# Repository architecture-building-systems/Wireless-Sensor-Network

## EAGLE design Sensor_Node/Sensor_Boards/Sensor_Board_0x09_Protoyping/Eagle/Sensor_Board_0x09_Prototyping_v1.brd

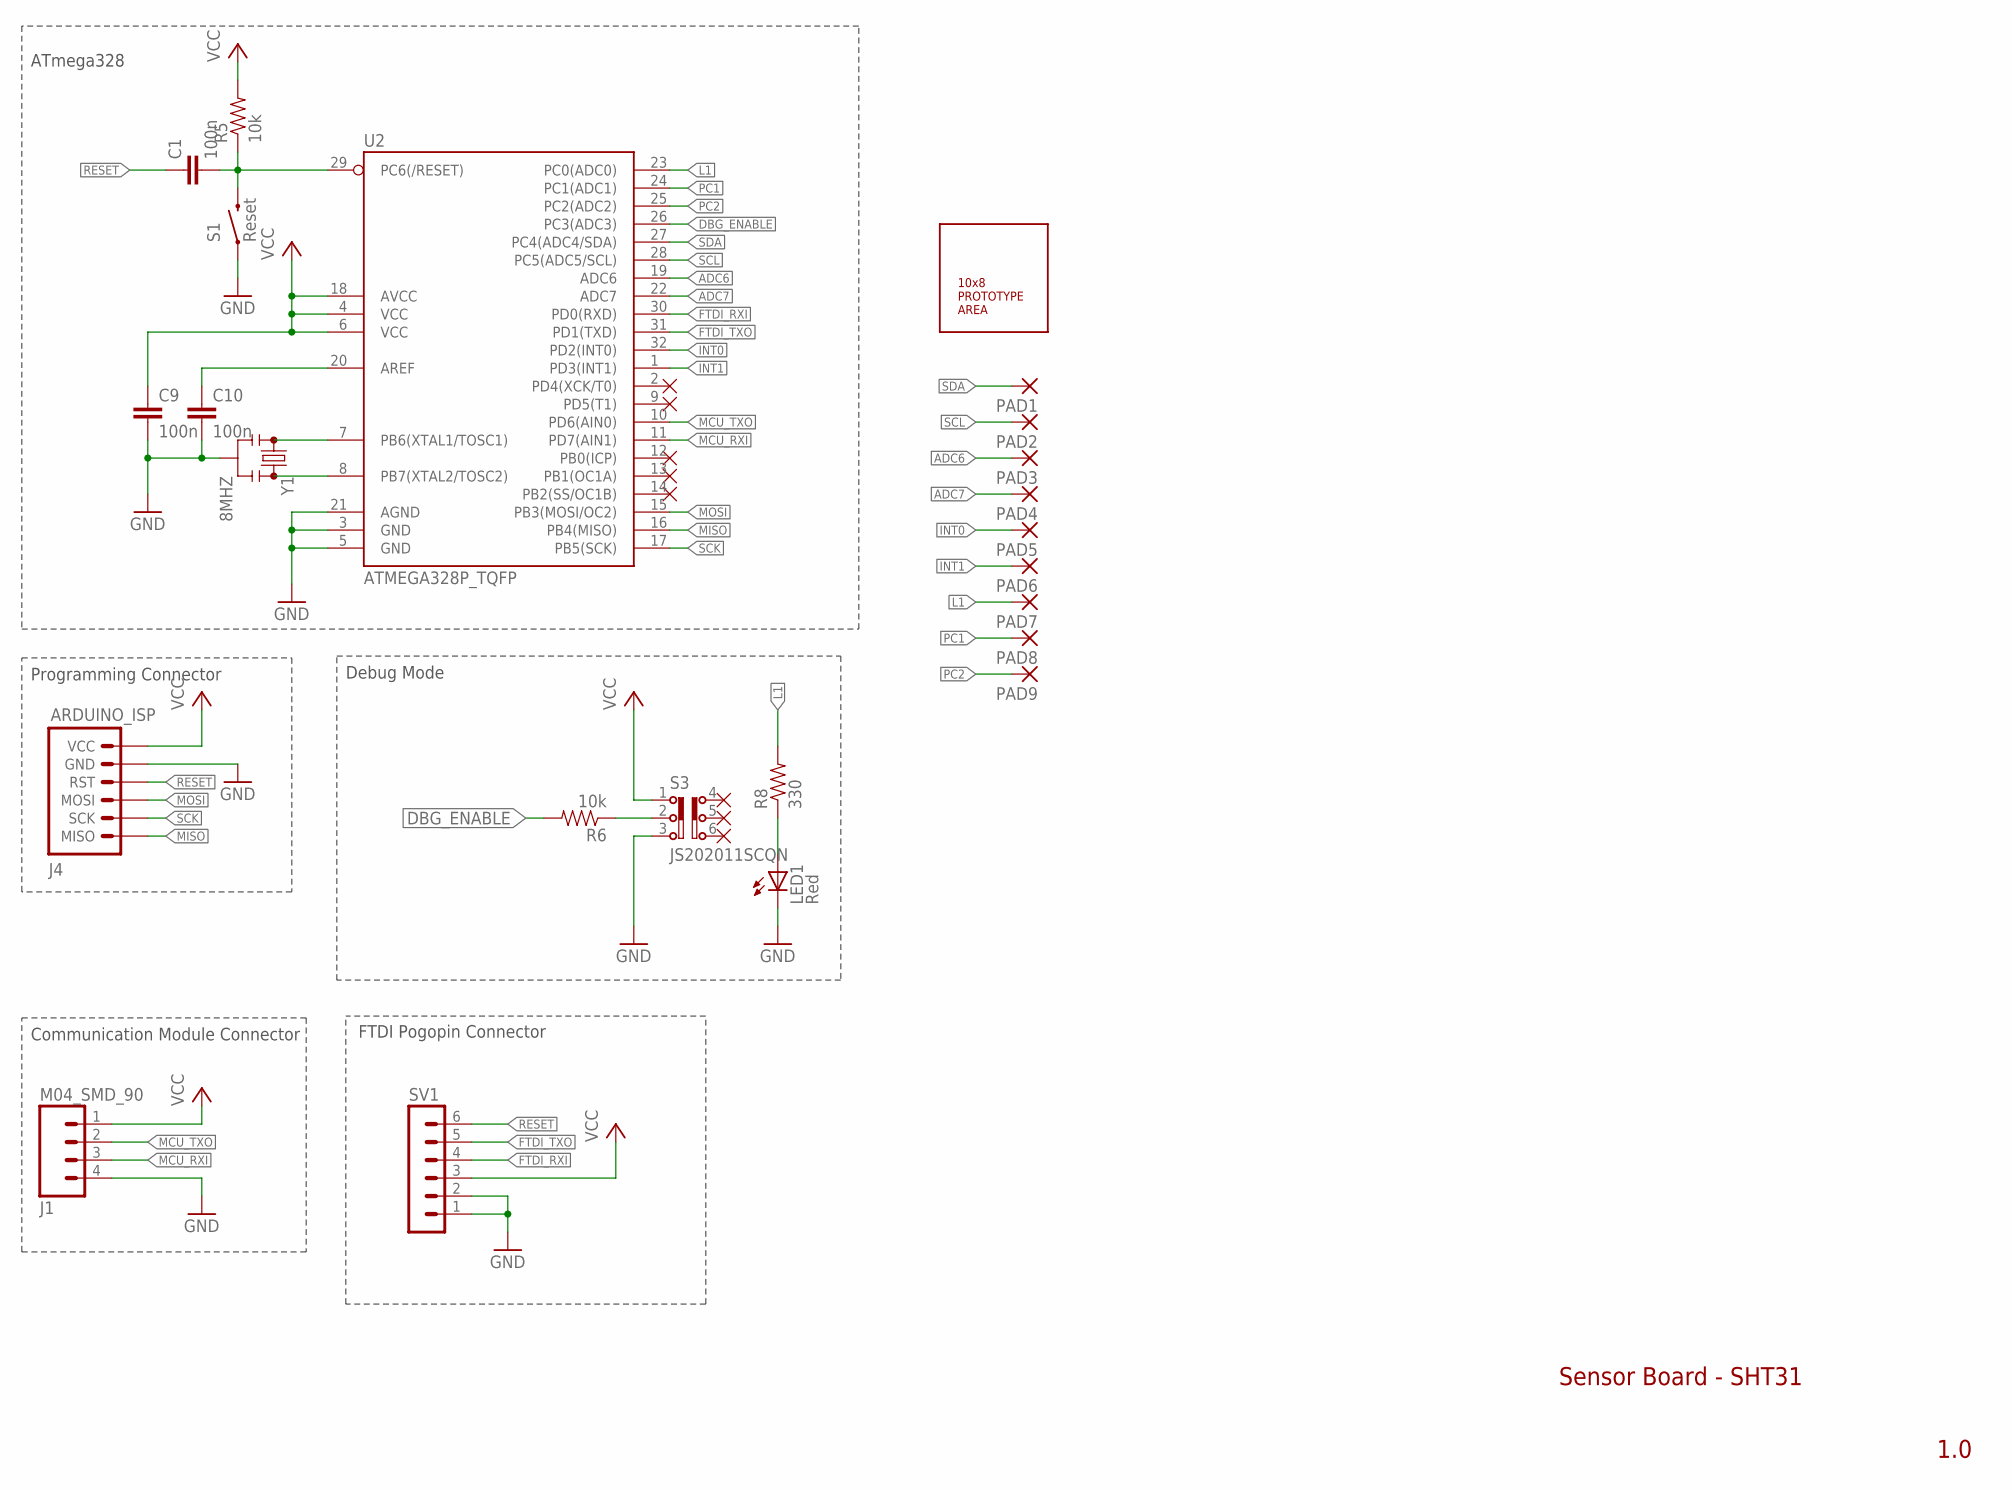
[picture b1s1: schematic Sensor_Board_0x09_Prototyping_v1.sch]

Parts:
C1, C9, C10: 100n; C0805
J1: M04_SMD_90
J4: ARDUINO_ISP; M-2X3
LED1: Red; SML0805
PAD1, PAD2, PAD3, PAD4, PAD5, PAD6, PAD7, PAD8, PAD9: 1,6/0,9
R5, R6: 10k; 0805
R8: 330; 0805
S1: Reset; M-PUSHBUTTON-SMD
S3: JS202011SCQN
SV1: MA06-1
U2: ATMEGA328P_TQFP; TQFP32-08
U$1: 10X8_PROTOTYPE_AREA
Y1: 8MHZ; RESONATOR-SMD

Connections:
ADC6: PAD3.1, U2.19 (ADC6)
ADC7: PAD4.1, U2.22 (ADC7)
DBG_ENABLE: R6.2, U2.26 (PC3(ADC3))
FTDI_RXI: SV1.4, U2.30 (PD0(RXD))
FTDI_TXO: SV1.5, U2.31 (PD1(TXD))
GND: C9.2, C10.2, J1.4, J4.P$5 (GND), LED1.C, S1.1 (LEFT), S1.2 (LEFT), S3.3, SV1.1, SV1.2, U2.3 (GND), U2.5 (GND), U2.21 (AGND), Y1.2
INT0: PAD5.1, U2.32 (PD2(INT0))
INT1: PAD6.1, U2.1 (PD3(INT1))
L1: PAD7.1, R8.2, U2.23 (PC0(ADC0))
MCU_RXI: J1.3, U2.11 (PD7(AIN1))
MCU_TXO: J1.2, U2.10 (PD6(AIN0))
MISO: J4.P$1 (MISO), U2.16 (PB4(MISO))
MOSI: J4.P$3 (MOSI), U2.15 (PB3(MOSI/OC2))
unnamed: U2.8 (PB7(XTAL2/TOSC2)), Y1.3
unnamed: U2.7 (PB6(XTAL1/TOSC1)), Y1.1
unnamed: R6.1, S3.2
unnamed: C1.2, R5.1, S1.3 (RIGHT), S1.4 (RIGHT), U2.29 (PC6(/RESET))
unnamed: C10.1, U2.20 (AREF)
unnamed: LED1.A, R8.1
PC1: PAD8.1, U2.24 (PC1(ADC1))
PC2: PAD9.1, U2.25 (PC2(ADC2))
RESET: C1.1, J4.P$4 (RST), SV1.6
SCK: J4.P$2 (SCK), U2.17 (PB5(SCK))
SCL: PAD2.1, U2.28 (PC5(ADC5/SCL))
SDA: PAD1.1, U2.27 (PC4(ADC4/SDA))
VCC: C9.1, J1.1, J4.P$6 (VCC), R5.2, S3.1, SV1.3, U2.4 (VCC), U2.6 (VCC), U2.18 (AVCC)

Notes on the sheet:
Debug Mode
Programming Connector
ATmega328
Communication Module Connector
Sensor Board - SHT31
1.0
FTDI Pogopin Connector

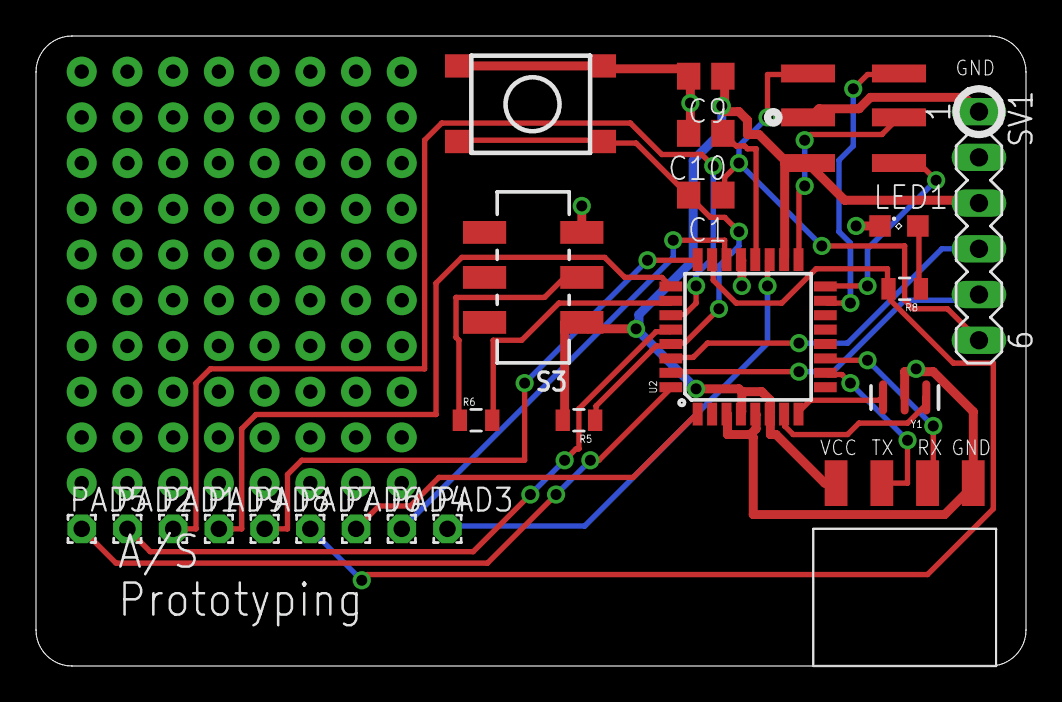
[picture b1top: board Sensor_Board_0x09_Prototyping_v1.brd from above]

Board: 2 copper layers, 55.0 x 35.0 mm, 24 parts (0 on the bottom side), 26 nets.

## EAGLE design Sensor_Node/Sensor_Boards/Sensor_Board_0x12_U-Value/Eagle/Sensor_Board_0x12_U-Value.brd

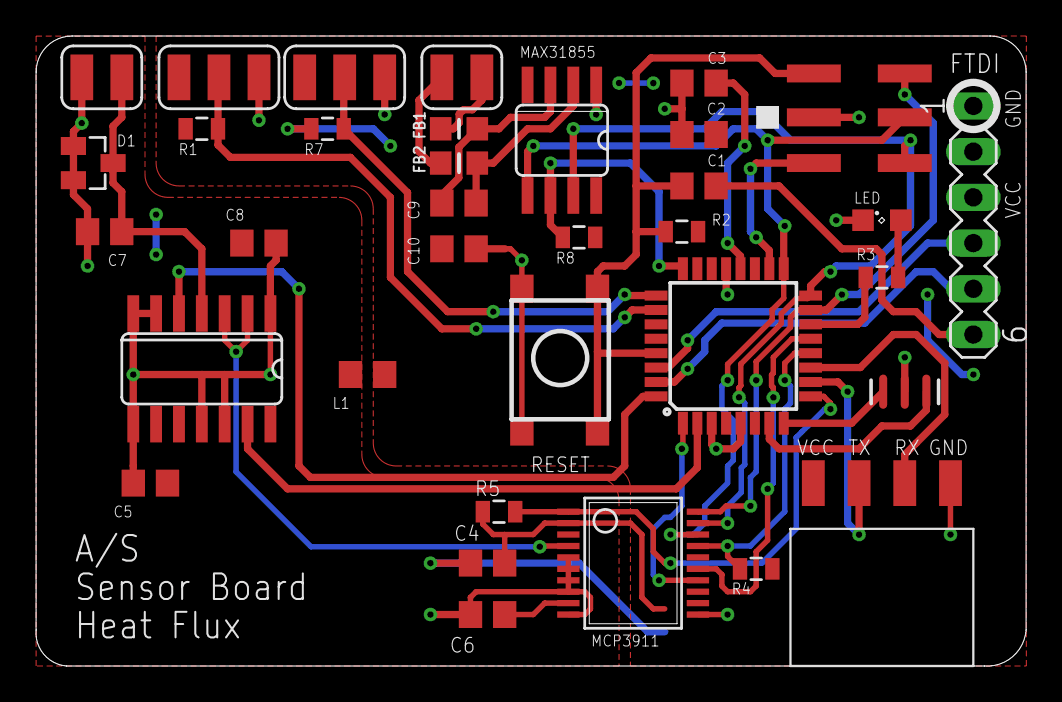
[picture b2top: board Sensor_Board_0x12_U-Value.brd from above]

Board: 2 copper layers, 55.0 x 35.0 mm, 42 parts (1 on the bottom side), 34 nets.

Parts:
C1, C2, C3, C4, C5, C6, C8, C10: 100n; C0805
C7: 1u; C0805
C9: 10n; C0805
D1: LEDXLAMP_BAV99; LEDXLAMP_SOT23
FB1, FB2: MICROBUILDER__0805MP
IC1: MCP3911; HEATFLOW_SSOP20
IC2: 40XX_4066D; 40XX_SO14
IC4: MAX31855; ADAFRUIT_SO08
J1: M04_SMD_90
J4: ARDUINO_ISP; M-2X3
L1: HEATFLOW2_74279220601; HEATFLOW2_0805
LED: Red; SML0805
PAD1, PAD2, PAD3, PAD4, PAD5, PAD6, PAD7, PAD8, PAD9, PAD10: WIREPADSMD1,27-254; SMD1,27-2,54
R1, R2, R4, R5, R7, R8: 10k; 0805
R3: 330; 0805
R6: 0; RESISTOR_M0805
S1: Reset; M-PUSHBUTTON-SMD
SV1: MA06-1
U2: ATMEGA328P_TQFP; TQFP32-08
Y1: 8MHZ; RESONATOR-SMD

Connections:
AGND: C4.1, C5.2, C7.2, C8.2, D1.1, D1.2, IC1.5, IC1.6, IC1.7, IC1.8, IC1.10, IC2.1, IC2.6, IC2.7, IC2.8, IC2.11, IC2.12, PAD2.1, R6.2
AVCC: C5.1, C8.1, IC1.3, IC2.14, L1.2
DGND: C2.2, C3.2, C6.2, C10.2, IC1.11, IC4.1, J1.4, J4.P$5, LED.C, PAD5.1, PAD8.1, R6.1, S1.1, S1.2, SV1.1, SV1.2, U2.3, U2.5, U2.21, Y1.2
DS18B20_DATA_1: PAD4.1, R1.1, U2.26
DS18B20_DATA_2: PAD7.1, R7.1, U2.25
DVCC: C2.1, C6.1, C10.1, IC1.2, IC4.4, J1.1, J4.P$6, L1.1, PAD3.1, PAD6.1, R1.2, R2.2, R4.2, R5.2, R7.2, R8.2, SV1.3, U2.4, U2.6, U2.18
FTDI_RESET: C1.1, SV1.6
FTDI_RXI: SV1.4, U2.30
FTDI_TXO: SV1.5, U2.31
INPUT_EN: IC2.5, U2.32
INPUT_SHORT: IC2.13, U2.2
L1: R3.2, U2.14
MAX_CS: IC4.6, R8.1, U2.24
MCP_CLK: IC1.15, U2.13
MCP_CS: IC1.17, R4.1, U2.12
MCP_DATA_RDY: IC1.14, U2.1
MCP_RESET: IC1.1, R5.1, U2.9
MCU_RXI: J1.3, U2.11
MCU_TXO: J1.2, U2.10
MISO: IC1.19, IC4.7, J4.P$1, U2.16
MOSI: IC1.20, J4.P$3, U2.15
unnamed: U2.8, Y1.3
unnamed: U2.7, Y1.1
unnamed: FB1.1, PAD9.1
unnamed: C4.2, IC1.9
unnamed: IC1.4, IC2.2, IC2.3
unnamed: C7.1, D1.3, IC2.4, PAD1.1
unnamed: FB2.1, PAD10.1
unnamed: C9.2, FB2.2, IC4.2
unnamed: C9.1, FB1.2, IC4.3
unnamed: C3.1, U2.20
unnamed: LED.A, R3.1
RESET: C1.2, J4.P$4, R2.1, S1.3, S1.4, U2.29
SCK: IC1.18, IC4.5, J4.P$2, U2.17

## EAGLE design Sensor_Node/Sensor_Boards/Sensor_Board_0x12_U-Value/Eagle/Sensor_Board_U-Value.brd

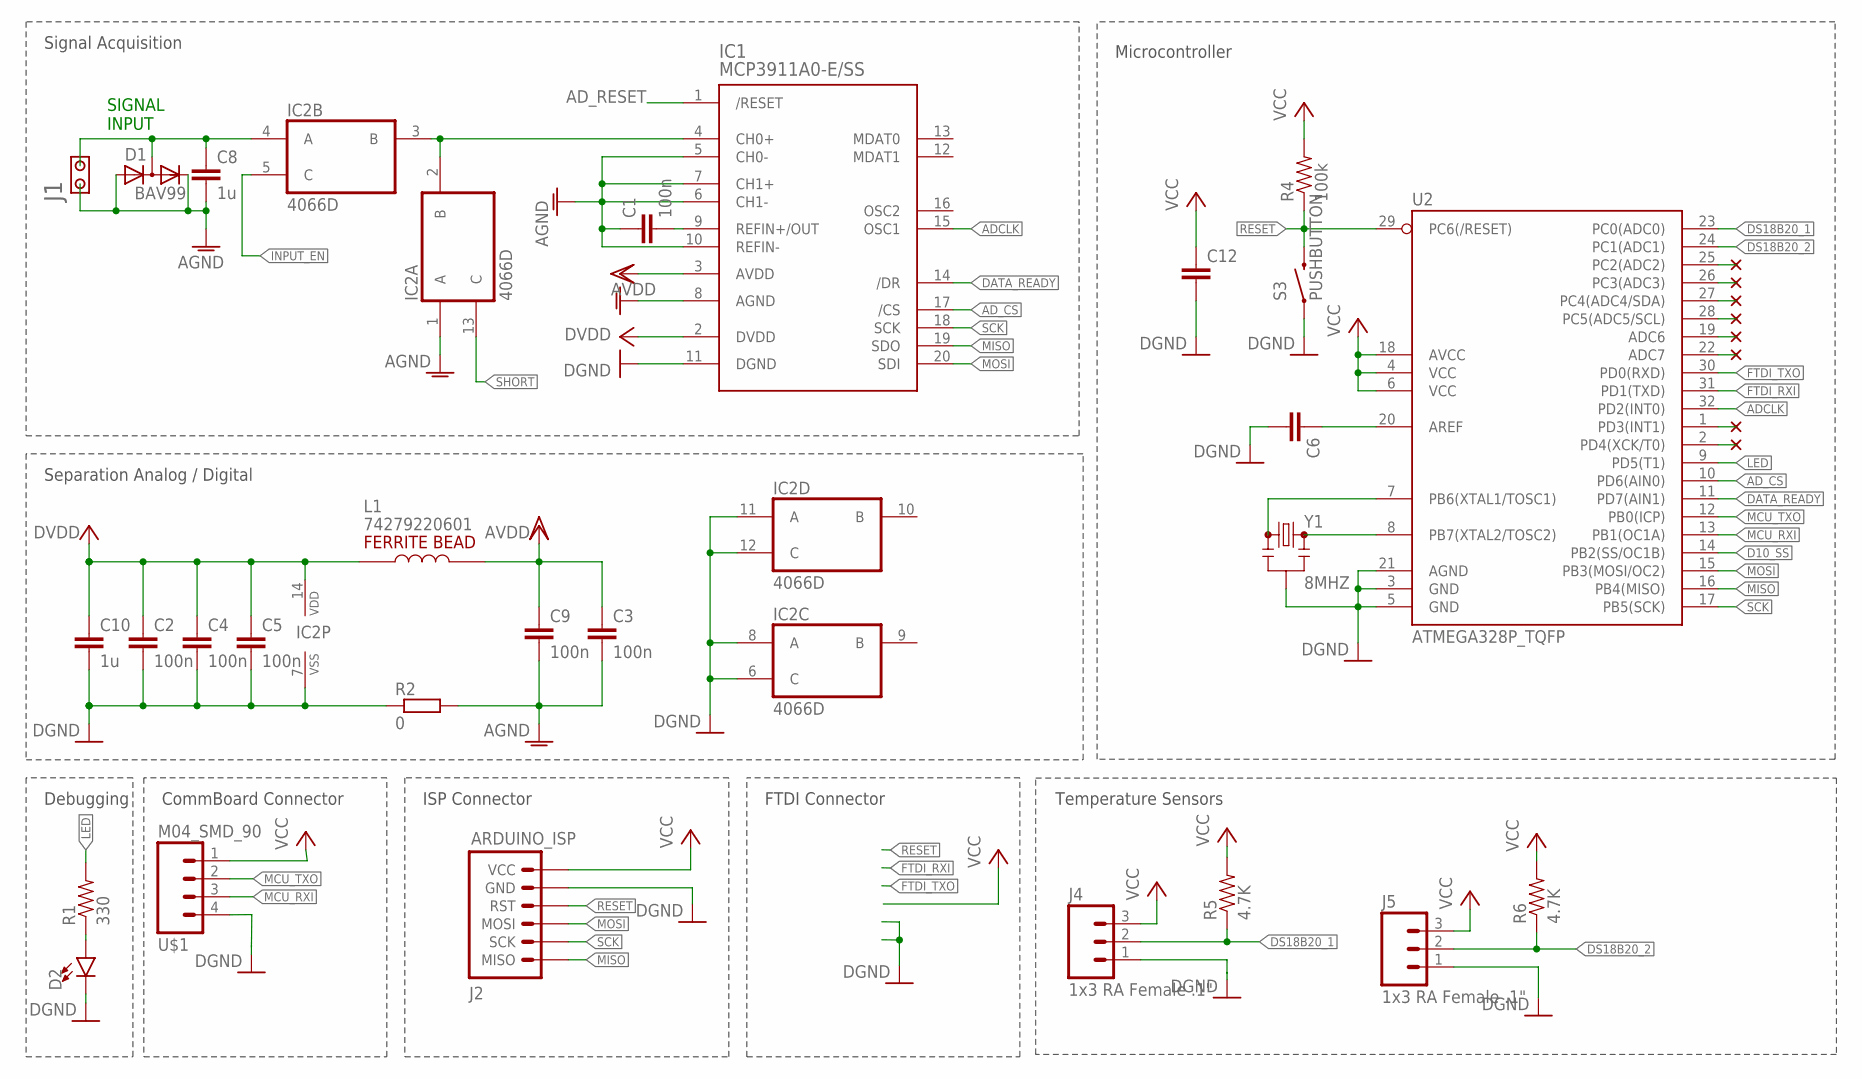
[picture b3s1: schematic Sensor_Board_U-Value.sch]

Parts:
C1, C2, C3, C4, C5, C9: 100n; C0805
C6, C12: CAP0805; 0805
C8, C10: 1u; C0805
D1: BAV99; SOT23
D2: LED0603; LED-0603
IC1: MCP3911A0-E/SS; SSOP20
IC2: 4066D; SO14
J1: CON2X1
J2: ARDUINO_ISP; M-2X3
J4, J5: 1x3 RA Female .1"; 1X03_SMD_RA_FEMALE
L1: 74279220601; 0805
R1: 330; 0805
R2: 0; M0805
R4: 100k; 0805
R5, R6: 4.7K; 0805
S3: PUSHBUTTON; M-PUSHBUTTON-SMD
U2: ATMEGA328P_TQFP; TQFP32-08
U$1: M04_SMD_90
Y1: 8MHZ; RESONATOR-SMD

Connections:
ADCLK: IC1.15 (OSC1), U2.32 (PD2(INT0))
AD_CS: IC1.17 (/CS), U2.10 (PD6(AIN0))
AD_RESET: IC1.1 (/RESET)
AGND: C1.1, C3.2, C8.2, C9.2, D1.1 (A), D1.2 (C), IC1.5 (CH0-), IC1.6 (CH1-), IC1.7 (CH1+), IC1.8 (AGND), IC1.10 (REFIN-), IC2.1 (A), J1.1, R2.2
AVDD: C3.1, C9.1, IC1.3 (AVDD), L1.2
D10_SS: U2.14 (PB2(SS/OC1B))
DATA_READY: IC1.14 (/DR), U2.11 (PD7(AIN1))
DGND: C2.2, C4.2, C5.2, C10.2, IC1.11 (DGND), IC2.6 (C), IC2.7 (VSS), IC2.8 (A), IC2.11 (A), IC2.12 (C), R2.1
DS18B20_1: J4.2, R5.1, U2.23 (PC0(ADC0))
DS18B20_2: J5.2, R6.1, U2.24 (PC1(ADC1))
DVDD: C2.1, C4.1, C5.1, C10.1, IC1.2 (DVDD), IC2.14 (VDD), L1.1
FTDI_RXI: U2.31 (PD1(TXD))
FTDI_TXO: U2.30 (PD0(RXD))
GND: C6.2, C12.2, D2.C, J2.P$5 (GND), J5.1, S3.1 (LEFT), S3.2 (LEFT), U2.3 (GND), U2.5 (GND), U2.21 (AGND), Y1.2
INPUT_EN: IC2.5 (C)
LED: R1.2, U2.9 (PD5(T1))
MCU_RXI: U2.13 (PB1(OC1A)), U$1.3
MCU_TXO: U2.12 (PB0(ICP)), U$1.2
MISO: IC1.19 (SDO), J2.P$1 (MISO), U2.16 (PB4(MISO))
MOSI: IC1.20 (SDI), J2.P$3 (MOSI), U2.15 (PB3(MOSI/OC2))
unnamed: C1.2, IC1.9 (REFIN+/OUT)
unnamed: C6.1, U2.20 (AREF)
unnamed: IC1.4 (CH0+), IC2.2 (B), IC2.3 (B)
unnamed: C8.1, D1.3 (AC), IC2.4 (A), J1.2
unnamed: U2.8 (PB7(XTAL2/TOSC2)), Y1.3
unnamed: D2.A, R1.1
unnamed: U2.7 (PB6(XTAL1/TOSC1)), Y1.1
RESET: J2.P$4 (RST), R4.1, S3.3 (RIGHT), S3.4 (RIGHT), U2.29 (PC6(/RESET))
SCK: IC1.18 (SCK), J2.P$2 (SCK), U2.17 (PB5(SCK))
SHORT: IC2.13 (C)
VCC: C12.1, J2.P$6 (VCC), J4.3, J5.3, R4.2, R5.2, R6.2, U2.4 (VCC), U2.6 (VCC), U2.18 (AVCC), U$1.1

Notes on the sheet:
SIGNAL INPUT
Debugging
Microcontroller
Signal Acquisition
Separation Analog / Digital
CommBoard Connector
ISP Connector
FTDI Connector
Temperature Sensors

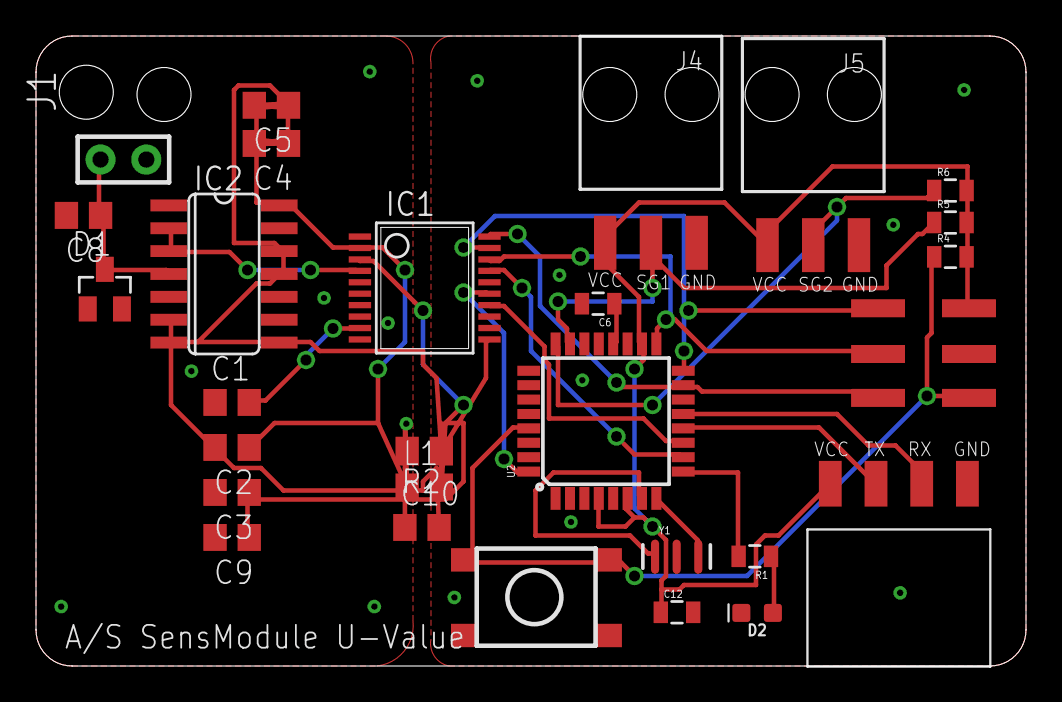
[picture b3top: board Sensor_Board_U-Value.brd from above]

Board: 2 copper layers, 55.0 x 35.0 mm, 28 parts (0 on the bottom side), 25 nets.

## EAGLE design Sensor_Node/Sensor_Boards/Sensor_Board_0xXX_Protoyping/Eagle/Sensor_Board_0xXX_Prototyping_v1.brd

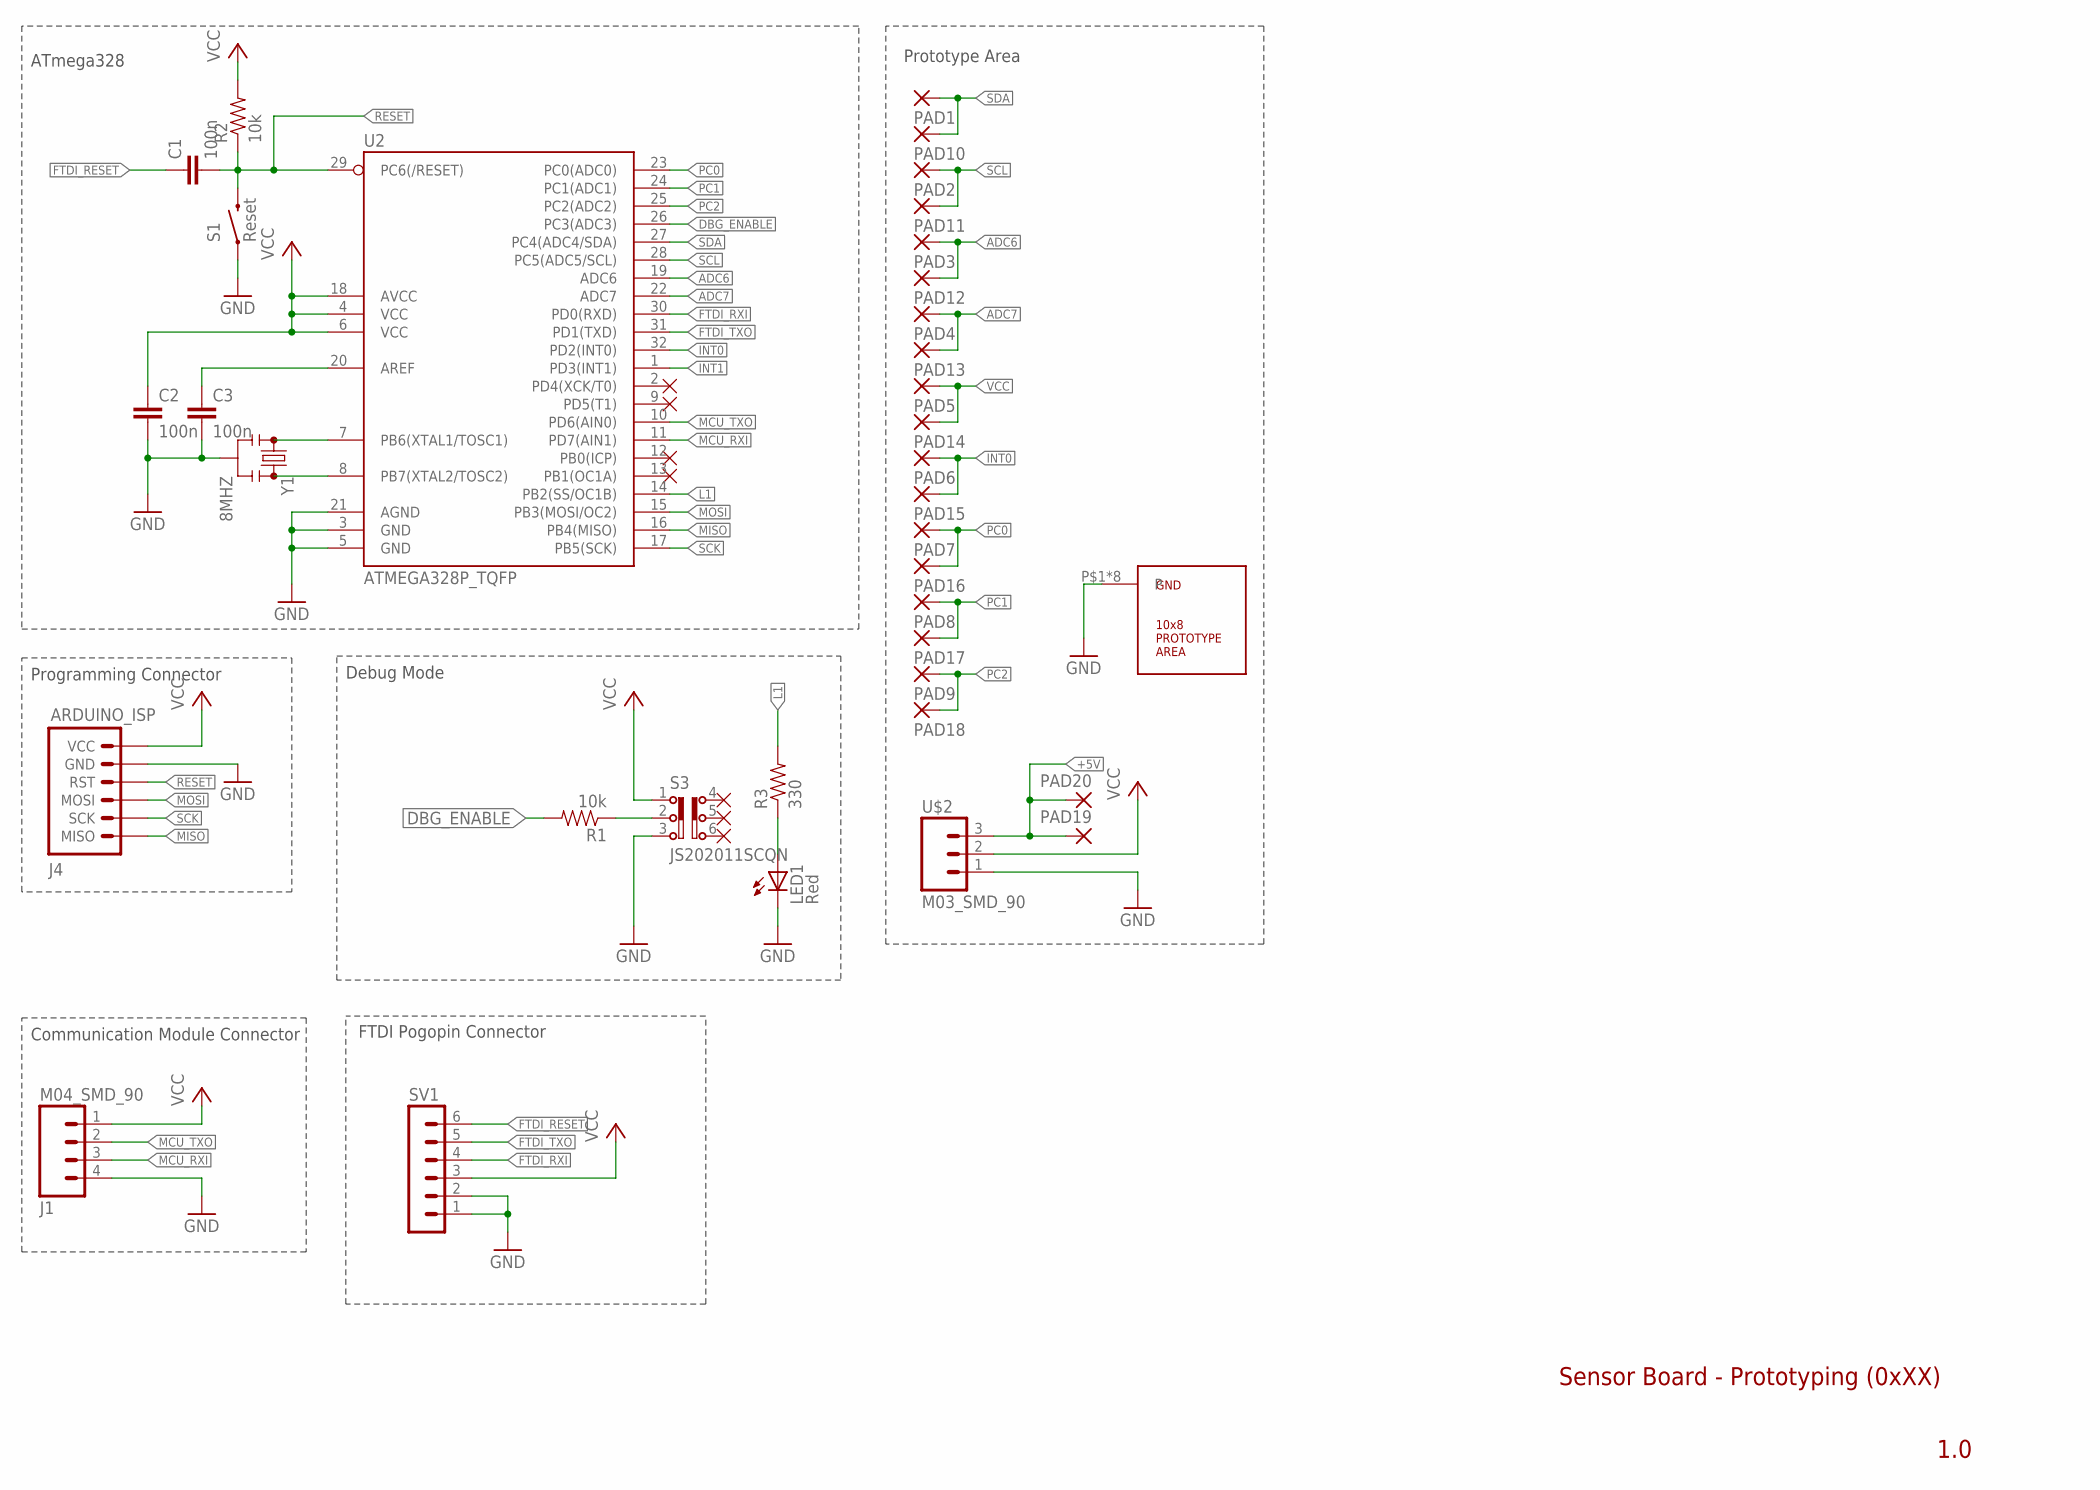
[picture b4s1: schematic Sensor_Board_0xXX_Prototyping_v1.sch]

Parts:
C1, C2, C3: 100n; C0805
J1: M04_SMD_90
J4: ARDUINO_ISP; M-2X3
LED1: Red; SML0805
PAD1, PAD2, PAD3, PAD4, PAD5, PAD6, PAD7, PAD8, PAD9, PAD10, PAD11, PAD12, PAD13, PAD14, PAD15, PAD16, PAD17, PAD18, PAD19, PAD20: 1,6/0,9
R1, R2: 10k; 0805
R3: 330; 0805
S1: Reset; M-PUSHBUTTON-SMD
S3: JS202011SCQN
SV1: MA06-1
U2: ATMEGA328P_TQFP; TQFP32-08
U$1: 10X8_PROTOTYPE_AREA
U$2: M03_SMD_90
Y1: 8MHZ; RESONATOR-SMD

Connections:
+5V: PAD19.1, PAD20.1, U$2.3
ADC6: PAD3.1, PAD12.1, U2.19 (ADC6)
ADC7: PAD4.1, PAD13.1, U2.22 (ADC7)
DBG_ENABLE: R1.2, U2.26 (PC3(ADC3))
FTDI_RESET: C1.1, SV1.6
FTDI_RXI: SV1.4, U2.30 (PD0(RXD))
FTDI_TXO: SV1.5, U2.31 (PD1(TXD))
GND: C2.2, C3.2, J1.4, J4.P$5 (GND), LED1.C, S1.1 (LEFT), S1.2 (LEFT), S3.3, SV1.1, SV1.2, U2.3 (GND), U2.5 (GND), U2.21 (AGND), U$1.P$1, U$1.P$2, U$1.P$3, U$1.P$4, U$1.P$5, U$1.P$6, U$1.P$7, U$1.P$8, U$2.1, Y1.2
INT0: PAD6.1, PAD15.1, U2.32 (PD2(INT0))
INT1: U2.1 (PD3(INT1))
L1: R3.2, U2.14 (PB2(SS/OC1B))
MCU_RXI: J1.3, U2.11 (PD7(AIN1))
MCU_TXO: J1.2, U2.10 (PD6(AIN0))
MISO: J4.P$1 (MISO), U2.16 (PB4(MISO))
MOSI: J4.P$3 (MOSI), U2.15 (PB3(MOSI/OC2))
unnamed: U2.8 (PB7(XTAL2/TOSC2)), Y1.3
unnamed: U2.7 (PB6(XTAL1/TOSC1)), Y1.1
unnamed: R1.1, S3.2
unnamed: C3.1, U2.20 (AREF)
unnamed: LED1.A, R3.1
PC0: PAD7.1, PAD16.1, U2.23 (PC0(ADC0))
PC1: PAD8.1, PAD17.1, U2.24 (PC1(ADC1))
PC2: PAD9.1, PAD18.1, U2.25 (PC2(ADC2))
RESET: C1.2, J4.P$4 (RST), R2.1, S1.3 (RIGHT), S1.4 (RIGHT), U2.29 (PC6(/RESET))
SCK: J4.P$2 (SCK), U2.17 (PB5(SCK))
SCL: PAD2.1, PAD11.1, U2.28 (PC5(ADC5/SCL))
SDA: PAD1.1, PAD10.1, U2.27 (PC4(ADC4/SDA))
VCC: C2.1, J1.1, J4.P$6 (VCC), PAD5.1, PAD14.1, R2.2, S3.1, SV1.3, U2.4 (VCC), U2.6 (VCC), U2.18 (AVCC), U$2.2

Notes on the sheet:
Debug Mode
Programming Connector
ATmega328
Communication Module Connector
Sensor Board - Prototyping (0xXX)
1.0
FTDI Pogopin Connector
Prototype Area

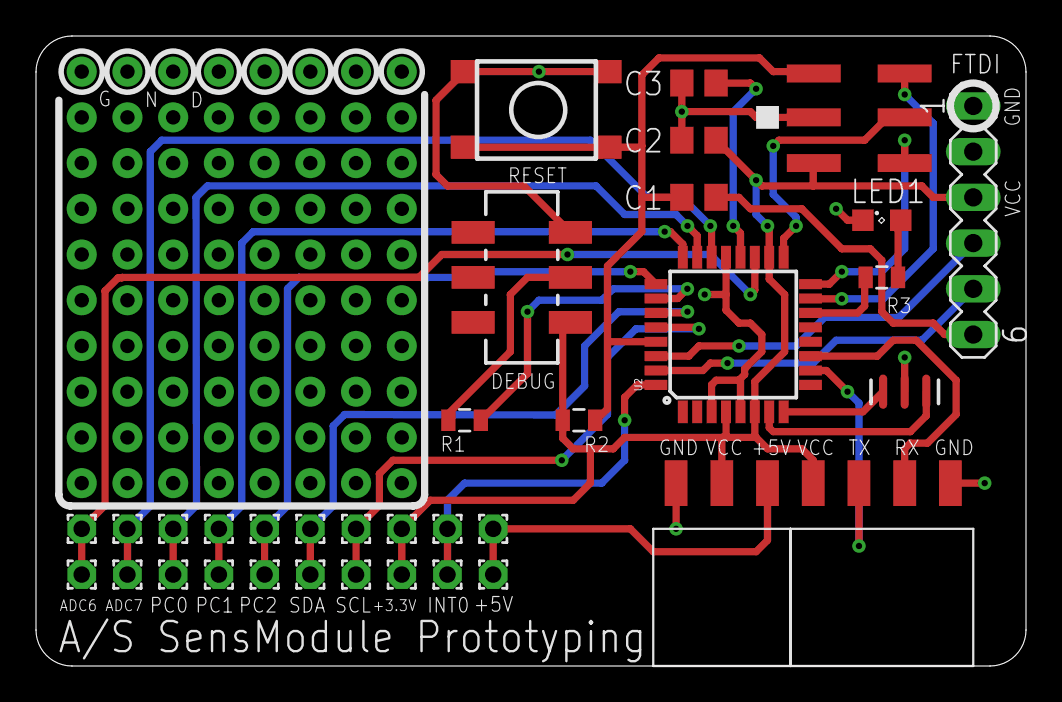
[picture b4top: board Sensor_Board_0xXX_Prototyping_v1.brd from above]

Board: 2 copper layers, 55.0 x 35.0 mm, 36 parts (0 on the bottom side), 27 nets.

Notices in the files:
parts and their libraries:
SparkFun-Passives: Licensing: Creative Commons ShareAlike 4.0 International - https://creativecommons.org/licenses/by-sa/4.0
